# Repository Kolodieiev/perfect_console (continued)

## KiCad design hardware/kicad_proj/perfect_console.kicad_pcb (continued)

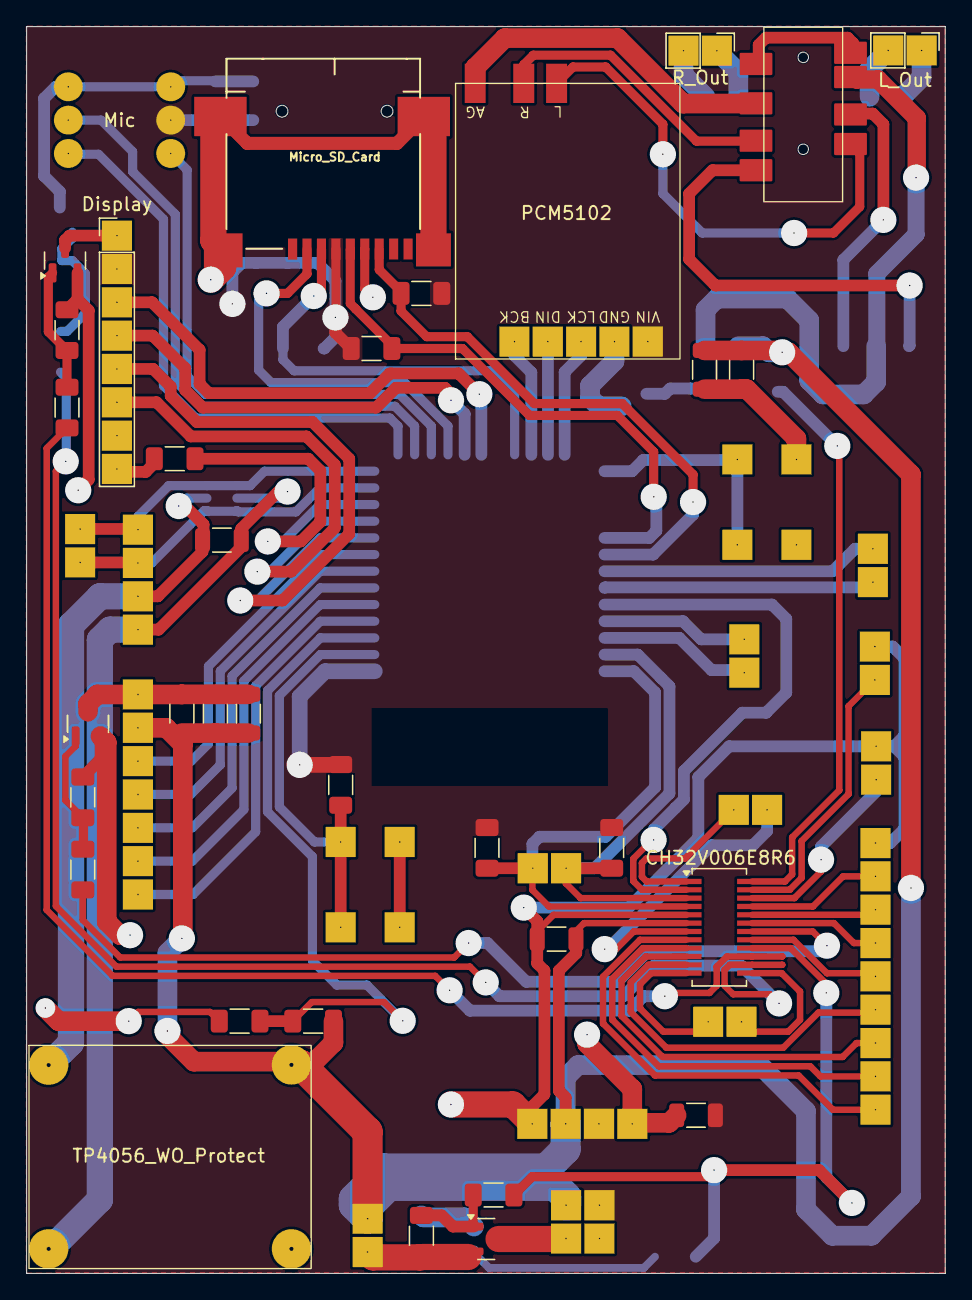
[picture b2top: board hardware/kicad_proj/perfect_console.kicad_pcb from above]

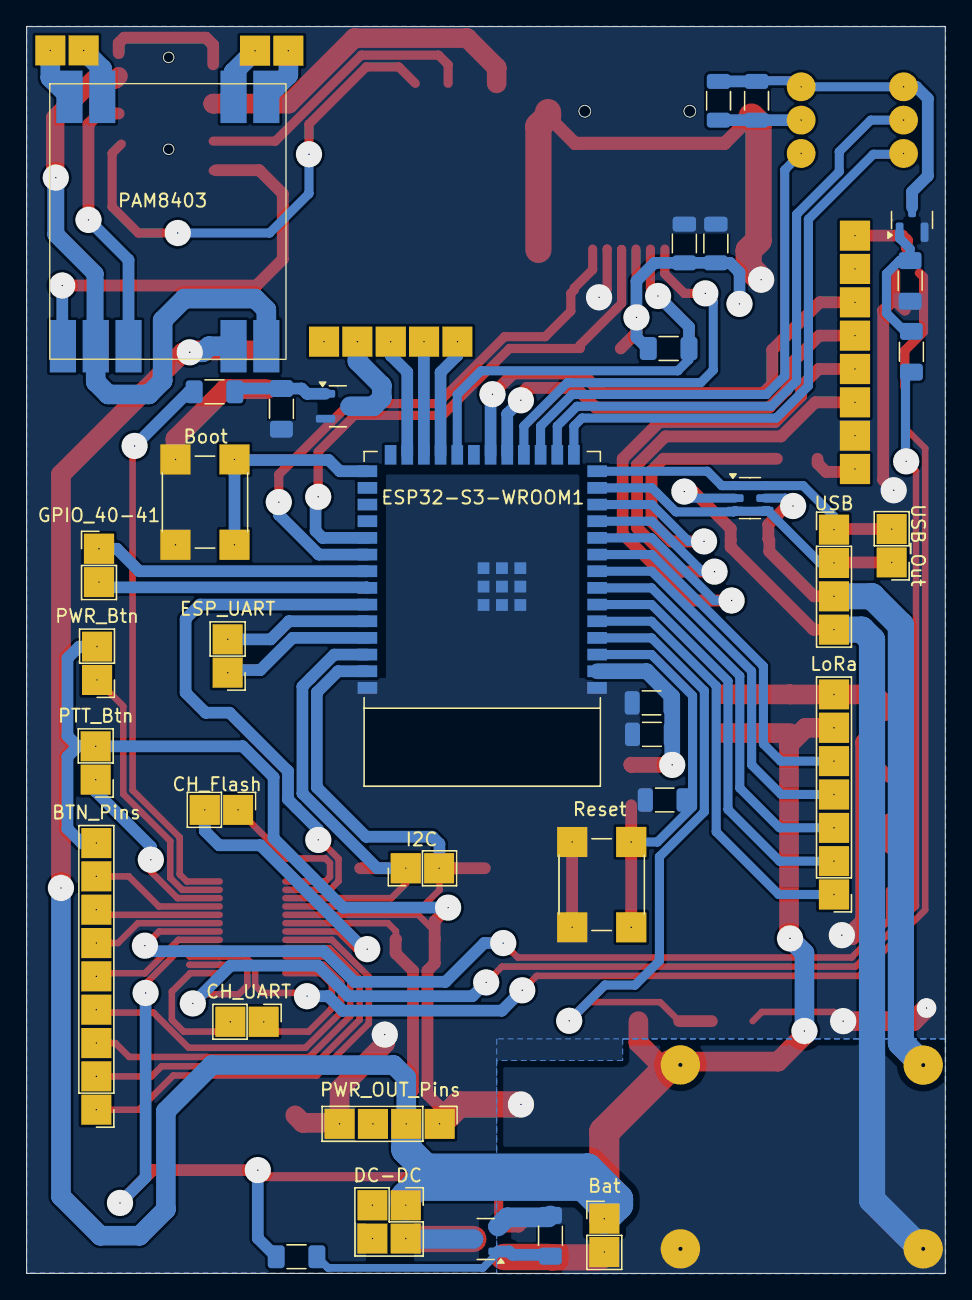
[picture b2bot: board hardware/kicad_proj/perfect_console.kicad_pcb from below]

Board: 2 copper layers, 70.0 x 95.0 mm, 70 parts (36 on the bottom side), 78 nets.

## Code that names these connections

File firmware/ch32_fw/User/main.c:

#include <debug.h>
#include <gpio.h>
#include <i2c_slave.h>
#include "input.h"
#include "touch.h"
#include "CoprocessorCMD.h"

// #define DEBUG_LOG

//------------------------------------------------------------------------------------------------------------- btns
#define BTNS_NUM 7

#define PIN_POWER_BTN 23

#define PIN_PTT_BTN 22
#define PIN_OK_BTN 19
#define PIN_BACK_BTN 8
#define PIN_LEFT_BTN 11
#define PIN_RIGHT_BTN 17
#define PIN_UP_BTN 9
#define PIN_DOWN_BTN 10

#define PIN_PB1 20
#define PIN_PB3 21

#define INPUT_UPD_TIME_MS 10

//------------------------------------------------------------------------------------------------------------- keys
#define PIN_MIC_KEY 14
#define PIN_DISPLAY_KEY 15
#define PIN_POWER_KEY 16
#define PIN_LORA_KEY 18
#define PIN_AUDIO_OUT_KEY 24

#define PIN_I2C_INT 2

//------------------------------------------------------------------------------------------------------------- i2c

#define BTNS_NUM_BUFF_SIZE ((BTNS_NUM + 7) / 8)
#define I2C_TEMP_BUFF_SIZE 5

#define I2C_FREQ 100000
#define RX_ADDR 0x66

//

volatile uint8_t _data_size_to_send = 0;
uint8_t _i2c_out_buff[I2C_TEMP_BUFF_SIZE] = {0};
uint8_t _btns_state_buff[BTNS_NUM_BUFF_SIZE] = {0};

//------------------------------------------------------------------------------------------------------------- power
#define TIME_TO_TOGGLE_PWR 3000
uint8_t _is_sleeping = 0;

//------------------------------------------------------------------------------------------------------------- func
void initPins (void);
void deinitPins (void);

void initPwrBtnExti (void);
void deinitPwrBtnExti (void);

void goToSleep (void);
void wakeUp (void);
void EXTI7_0_IRQHandler (void) __attribute__ ((interrupt ("WCH-Interrupt-fast")));

void i2c_read_handler (const uint8_t *in_buff, uint8_t in_buff_size);
void i2c_write_handler (uint8_t *out_buff, volatile uint8_t *out_buff_size);

int main (void) {
    NVIC_PriorityGroupConfig (NVIC_PriorityGroup_1);
    SystemCoreClockUpdate();
    initMillis();
    initUsartPrintf (230400);

    //-----------------------

#ifdef DEBUG_LOG
    printf ("Begin...\r\n");
#endif

    pinMode (PIN_POWER_BTN, GPIO_Mode_IPU);
    initPins();
    enableI2CSlave (I2C_FREQ, RX_ADDR, i2c_read_handler, i2c_write_handler);
    goToSleep();

    unsigned long power_btn_press_time = 0;

    while (1) {
        if (_is_sleeping == 1) {
            if (digitalRead (PIN_POWER_BTN) == HIGH) {
                power_btn_press_time = 0;
#ifdef DEBUG_LOG
                printf ("PIN_POWER_BTN == HIGH\r\n");
#endif
                goToSleep();
            } else {
                if (power_btn_press_time == 0) {
                    power_btn_press_time = millis();
                } else if (millis() - power_btn_press_time > TIME_TO_TOGGLE_PWR) {
                    power_btn_press_time = 0;
                    wakeUp();
                }
            }

            continue;
        }

        if (digitalRead (PIN_POWER_BTN) == LOW) {
            if (power_btn_press_time == 0) {
                power_btn_press_time = millis();
            } else if (millis() - power_btn_press_time > TIME_TO_TOGGLE_PWR) {
                power_btn_press_time = 0;
                goToSleep();
            }

            continue;
        } else {
            power_btn_press_time = 0;
        }

        static unsigned long input_update_time = 0;
        if (millis() - input_update_time > INPUT_UPD_TIME_MS) {
            inputUpdate();
            loadInputState (_btns_state_buff);
            input_update_time = millis();
        }
    }
}

void initPins (void) {
#ifdef DEBUG_LOG
    printf ("initPins\r\n");
#endif

    pinMode (PIN_POWER_KEY, GPIO_Mode_Out_PP);
    digitalWrite (PIN_POWER_KEY, HIGH);

    pinMode (PIN_DISPLAY_KEY, GPIO_Mode_Out_PP);
    digitalWrite (PIN_DISPLAY_KEY, LOW);

    pinMode (PIN_AUDIO_OUT_KEY, GPIO_Mode_Out_PP);
    digitalWrite (PIN_AUDIO_OUT_KEY, LOW);

    pinMode (PIN_MIC_KEY, GPIO_Mode_Out_PP);
    digitalWrite (PIN_MIC_KEY, LOW);

    pinMode (PIN_LORA_KEY, GPIO_Mode_Out_PP);
    digitalWrite (PIN_LORA_KEY, LOW);

    enableInput (BTNS_NUM);

    addInputBtn (PIN_PTT_BTN);
    addInputBtn (PIN_OK_BTN);
    addInputBtn (PIN_BACK_BTN);
    addInputBtn (PIN_LEFT_BTN);
    addInputBtn (PIN_RIGHT_BTN);
    addInputBtn (PIN_UP_BTN);
    addInputBtn (PIN_DOWN_BTN);

    // addInputTouchBtn (PIN_OK_BTN);
    // addInputTouchBtn (PIN_BACK_BTN);
    // addInputTouchBtn (PIN_LEFT_BTN);
    // addInputTouchBtn (PIN_RIGHT_BTN);
    // addInputTouchBtn (PIN_UP_BTN);
    // addInputTouchBtn (PIN_DOWN_BTN);
}

void deinitPins (void) {
#ifdef DEBUG_LOG
    printf ("deinitPins\r\n");
#endif

    disableInput();
    disableTouchCap();

    pinMode (PIN_MIC_KEY, GPIO_Mode_IN_FLOATING);
    pinMode (PIN_DISPLAY_KEY, GPIO_Mode_IN_FLOATING);
    pinMode (PIN_POWER_KEY, GPIO_Mode_IN_FLOATING);
    pinMode (PIN_LORA_KEY, GPIO_Mode_IN_FLOATING);
    pinMode (PIN_AUDIO_OUT_KEY, GPIO_Mode_IN_FLOATING);
    pinMode (PIN_PTT_BTN, GPIO_Mode_IN_FLOATING);
    pinMode (PIN_OK_BTN, GPIO_Mode_IN_FLOATING);
    pinMode (PIN_BACK_BTN, GPIO_Mode_IN_FLOATING);
    pinMode (PIN_LEFT_BTN, GPIO_Mode_IN_FLOATING);
    pinMode (PIN_RIGHT_BTN, GPIO_Mode_IN_FLOATING);
    pinMode (PIN_UP_BTN, GPIO_Mode_IN_FLOATING);
    pinMode (PIN_DOWN_BTN, GPIO_Mode_IN_FLOATING);
}

void initPwrBtnExti (void) {
    RCC_PB2PeriphClockCmd (RCC_PB2Periph_AFIO, ENABLE);

    EXTI_InitTypeDef EXTI_InitStructure = {0};
    GPIO_EXTILineConfig (GPIO_PortSourceGPIOB, GPIO_PinSource1);
    EXTI_InitStructure.EXTI_Line = EXTI_Line1;
    EXTI_InitStructure.EXTI_Mode = EXTI_Mode_Interrupt;
    EXTI_InitStructure.EXTI_Trigger = EXTI_Trigger_Falling;
    EXTI_InitStructure.EXTI_LineCmd = ENABLE;
    EXTI_Init (&EXTI_InitStructure);

    NVIC_InitTypeDef NVIC_InitStructure = {0};
    NVIC_InitStructure.NVIC_IRQChannel = EXTI7_0_IRQn;
    NVIC_InitStructure.NVIC_IRQChannelPreemptionPriority = 1;
    NVIC_InitStructure.NVIC_IRQChannelSubPriority = 1;
    NVIC_InitStructure.NVIC_IRQChannelCmd = ENABLE;
    NVIC_Init (&NVIC_InitStructure);
}

void deinitPwrBtnExti (void) {
    EXTI_DeInit();
    NVIC_DisableIRQ (EXTI7_0_IRQn);
    RCC_PB2PeriphClockCmd (RCC_PB2Periph_AFIO, DISABLE);
}

void goToSleep (void) {
#ifdef DEBUG_LOG
    printf ("goToSleep\r\n");
#endif

    _is_sleeping = 1;
    initPwrBtnExti();
    deinitPins();
    PWR_EnterSTANDBYMode (PWR_STANDBYEntry_WFE);
}

void wakeUp (void) {
#ifdef DEBUG_LOG
    printf ("wakeUp\r\n");
#endif
    deinitPwrBtnExti();
    _is_sleeping = 0;
    initPins();
}

void EXTI7_0_IRQHandler (void) {
    if (EXTI_GetITStatus (EXTI_Line1) != RESET) {
#ifdef DEBUG_LOG
        printf ("EXTI\r\n");
#endif
        EXTI_ClearITPendingBit (EXTI_Line1);
    }
}

void i2c_read_handler (const uint8_t *in_buff, uint8_t in_buff_size) {
    CoprocessorCMD_t cmd = in_buff[0];
    switch (cmd) {
    case CCPU_CMD_GET_BTNS_STATE:
        memcpy (_i2c_out_buff, _btns_state_buff, BTNS_NUM_BUFF_SIZE);
        _data_size_to_send = BTNS_NUM_BUFF_SIZE;
        break;
    case CCPU_CMD_PIN_ON:
        if (in_buff_size < 2)
            return;
        digitalWrite (in_buff[1], HIGH);
        break;
    case CCPU_CMD_PIN_OFF:
        if (in_buff_size < 2)
            return;
        digitalWrite (in_buff[1], LOW);
        break;
    case CCPU_CMD_BTN_OFF:
        if (in_buff_size < 2)
            return;
        disableBtnByPos (in_buff[1]);
        break;
    case CCPU_CMD_BTN_ON:
        if (in_buff_size < 2)
            return;
        enableBtnByPos (in_buff[1]);
        break;
    case CCPU_CMD_DISABLE:
    case CCPU_CMD_ENABLE:
    default:
        return;
    }
}

void i2c_write_handler (uint8_t *out_buff, volatile uint8_t *out_buff_size) {
    *out_buff_size = _data_size_to_send;
    memcpy (out_buff, _i2c_out_buff, _data_size_to_send);
    for (uint32_t i = 0; i < _data_size_to_send; ++i)
        _i2c_out_buff[i] = 0;

    _data_size_to_send = 0;
}

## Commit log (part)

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2025-11-11 Незначні покращення
2025-11-11 Покращено взаємодію файлового менеджера з Linux
2025-11-12 Видалено TODO
2025-11-12 Додано головне ігрове меню
2025-11-12 Додано основні класи гри
2025-11-13 Перейменовано в RpgBaseScene
2025-11-13 Додано структуру для загального опису рівня
2025-11-13 Додано завантаження ресурсів рівня з диску
2025-11-13 Розширено тип маски прохідності спрайту
2025-11-13 Додано тип плитки
2025-11-14 Логування без перенесення рядка
2025-11-14 Виправлено ім'я задля уникнення перевантаження
2025-11-15 Видалено непотрібні файли
2025-11-15 Видалено неактуальні прапори збірки
2025-11-15 Виправлено некоректні параметри відкриття файлів
2025-11-15 Додано автоматичний завантажувач ресурсів поверхні
    Додано автоматичний завантажувач ресурсів поверхні сцени з диску.
2025-11-15 Додано повідомлення про відсутній ресурс
2025-11-15 Виправлено розміщення спрайтів
2025-11-15 Додано об'єкт персонажа
2025-11-15 Додано завантаження поверхні
2025-11-15 Видалено непотрібний параметр
    Менеджер ресурсів вже оголошено глобально
2025-11-15 Додано перевірку на 0 ідентифікатор
2025-11-15 Додано спрайт героя
2025-11-15 Додано скріншот
2025-12-22 Виправлено помилки в прикладі Lua
2025-12-22 Виправлено логіку малювання віджетів
2025-12-22 Виправлено помилку встановлення зображення
2025-12-22 Рефакторинг
2025-12-27 Виправлено(уточнено) імена методів
2025-12-28 Перенесено в контекст Lua
2025-12-28 Виправлення потенційних помилок
2025-12-28 Виправлено приведення типів до стилю С++
2025-12-28 Додано приклад роботи з SD
2025-12-28 Виправлено помилку, яка псувала купу
2026-01-06 Додано переривання надсилання файлу
2026-01-06 Додано прокручування тексту
2026-01-06 Виправлено документацію
2026-01-06 Додано відсутнє копіювання поля
2026-01-11 Видалено недосяжний код
2026-01-11 Магічні значення змінено на іменовані визначення
2026-01-11 Додано більше темного значення до кольору
2026-01-11 Виправлено помилку малювання фону
2026-01-12 Покращено сторінку надсилання файлу
2026-01-12 Зменшено глибину вкладення
2026-01-12 Додано відображення IP
2026-01-12 Додано фонове отримання файлів
2026-01-12 Виправлено логіку
2026-01-12 Видалено невикористану змінну
2026-01-13 Виправлено ім'я методу
2026-01-13 Імена функцій переміщено в масив
2026-01-13 Імена функцій переміщено до масиву
2026-01-13 Прибрано непотрібний else
2026-01-13 Додано обгортку для керування WiFi з Lua
2026-01-14 Виправлено методи
2026-01-16 Виправлено ім'я функції для уніфікації
2026-01-16 Виправлено помилку в прикладі
2026-01-16 Додано приклад керування wifi та запитів до web
2026-01-16 Додано return при некоректній к-сті параметрів
2026-01-16 Додано обгортку для Lua-serial
2026-01-16 Додано обгортку для Lua-web
2026-01-17 Переміщено в namespace
2026-01-18 Додано документацію
2026-01-18 Скорочено ланцюжок викликів
2026-01-19 Метод ініціалізації зроблено статичним
2026-01-19 Виклик методу замінено визначенням
2026-01-19 Оновлено підключення FileStream
2026-01-19 Додано підключення cstring
2026-01-20 Видалено статичність змінної
2026-01-20 Виправлено підключення FileStream
2026-01-20 Додано статичність методу
2026-01-20 Видалено неактуальний readme
2026-01-20 Налаштування об'єднано в graphics_setup.h
2026-01-21 Рефакторинг + документація
2026-01-21 Документація + рефакторинг
2026-01-23 Покращено документацію
2026-01-24 Виправлено некоректне визначення constexpr функції
2026-01-25 Виправлено ім'я типу
2026-01-25 Рефакторинг та документація
2026-01-25 MenuItem тепер потребує власний Image
2026-01-25 Додано перевірку типу вхідного об'єкта
2026-01-26 Виправлено шлях до зображення
2026-01-26 Додано перевірку належності до типу
2026-01-26 Додано readme
2026-01-26 Придушено попередження
2026-01-27 Додано підтримку завантаження списку файлів
2026-01-27 Неактуальний коментар
2026-01-29 Додано адаптивність форми
2026-01-29 Переписано на прямі виклики POSIX
2026-01-29 Додано підтримку видалення файлів
2026-01-30 Код WebServer додано в проект
2026-01-30 Усунуто спрацювання WDT
2026-01-30 Додано підтримку передзавантаження даних
2026-01-30 Оновлено розмір буферів сервера
2026-01-30 Приведено до коректного вигляду
2026-01-30 Виправлено русизми
2026-01-31 Додано правило для швидкої збірки
2026-02-01 Додано каркас документації
2026-02-01 Додано шаблон для майбутньої документації
2026-02-01 Додано про проєкт
2026-02-01 Оновлено Readme
2026-02-01 Виправлено тип заголовку
2026-02-02 Тему змінено на Furo
2026-02-06 Додано налаштування частоти ядра
2026-02-06 Додано підсвітку коду
2026-02-06 Додано визначення
2026-02-07 Видалено зайві відступи
2026-02-07 Налаштування відокремлено від фреймворку
2026-02-07 Виправлено шлях в include
2026-02-07 Додано новий каталог з налаштуваннями
2026-02-08 Спрощено виклик монтування карти пам'яті
2026-02-10 Виправлено вимкнення кнопок
2026-02-10 Виправлено некоректну логіку
2026-02-10 Видалено номер версії
2026-02-10 Уточнено опис класу
2026-02-10 Уточнено документацію
2026-02-11 Виправлено звернення до висячого вказівника
2026-02-14 Явно вказано версію C++
2026-02-14 Commit a63bfd9
2026-02-14 Commit 8440ae6
2026-02-14 Покращено перевірку монтування SD
2026-02-14 Видалено підтримку Doxygen
2026-02-14 Виправлено документацію методу
2026-02-14 Виправлено помилку в документації
2026-02-15 Виправлено документацію методів
2026-02-15 Покращено обробку читання хідера
2026-02-15 Додано відсутнє скидання прапору
2026-02-15 Видалено параметр за замовчуванням
2026-02-15 Виправлено місце встановлення прапору
2026-02-15 Додано документацію файлового менеджера
2026-02-18 Спрощено структуру каталогів
2026-02-18 Зменшено глибину вкладення каталогів
2026-02-18 Оновлено структуру проєкту Pixeler
2026-02-18 Виправлено шлях
2026-02-18 Додано перевірку відкриття файла
2026-02-20 Виправлено імена полів класу
2026-02-20 Об'єднано два методи отримання IP
2026-02-20 Оновлено ім'я методу
2026-02-20 Додано обробку некоректних значень
2026-02-20 Обробку винесено до WiFiManager
2026-02-20 Видалено зайву інформацію про помилку
2026-02-20 Додано налаштування потужності WiFi
2026-02-21 Додано завантаження налаштувань потужності модуля
2026-02-21 Видалено неактуальні рядкі
2026-02-21 Спрощено створення однотипного Label
2026-02-21 Спрощено генерацію Label для заголовка вікна
2026-02-21 Додано перевірку mutex-а
2026-02-21 Перейменовано AutoLock в MutexGuard
2026-02-21 Видалено блоки try-catch
2026-02-21 Виправлено перевірку mutex-a
2026-02-21 Додано значення за замовченням
2026-02-21 Виправлено налаштування cpp-check
2026-02-21 Виправлено попередження cpp-check
2026-02-21 Видалено невикористані поля
2026-02-22 Оновлено гербер-файли
2026-02-22 Додано маркування мосфетів
2026-02-22 Зменшено розміри плати
2026-02-22 Видалено креслення для ручного виготовлення
2026-03-15 Видалено непотрібний flush
2026-03-15 Додано відсутню залежність для Windows
2026-03-15 Видалено неактуальний todo
2026-03-15 Додано налаштування інвертування кольорів пікселів
2026-03-16 Виправлено редефайн
2026-03-16 Виправлено чергу команд ініціалізації дисплея
2026-03-16 Видалено дублювання коду
2026-03-16 Додано відсутнє взяття мютекса
2026-03-16 Додано метод отримання мютекса синхронізації
2026-03-16 Видалено перевірку малоймовірного випадку
2026-03-16 Додано підтримку декількох пристроїв на одному SPI
2026-03-17 Оновлено документацію
2026-03-17 Додано початкову ініціалізацію
2026-03-17 Видалено непотрібний sizeof
2026-03-17 Виправлено зміщення тексту
2026-03-20 Виправлено приклад lua-pwm
2026-03-20 Видалено приведення типу
2026-03-22 Зменшено значення одночасно відкритих файлів
2026-03-22 Видалено непотрібний include
2026-03-22 Увімкнуто вивід інформаційних повідомлень в термінал
2026-03-22 Покращено обробку ініціалізації шини SPI
2026-03-22 Додано таблицю розділів для esp32
2026-03-22 Додано сканер шини i2c
2026-03-23 Додано базовий клас для драйвера сенсорних екранів
2026-03-23 Додано підтримку сенсорних екранів в систему вводу
2026-03-23 Додано читання/запис з двобайтовою командою
2026-03-23 Виправлено імена методів менеджера i2c
2026-03-23 Додано пошук віджета за екранними координатами
2026-03-23 Додано інформацію про сенсорний ввід
2026-03-23 Додано налаштування сенсорного вводу
2026-03-24 Виправлено драйвер сенсорного екрана JC3248W535C
2026-03-24 Виправлено драйвер сенсорного екрана GT911
2026-03-24 Додано перевірку підключення сенсорного екрану
2026-03-24 Відключено підтримку сенсорного екрану в прошивці
2026-03-25 Виправлено прапор збірки
2026-03-26 Виправлено імена методів
2026-03-26 Виправлено розрахунок тривалості треку
2026-03-26 Видалено float операції
2026-03-26 Оптимізовано отримання семплу
2026-03-26 Додано підтримку сенсорного екрану
2026-03-28 Повернуто fluch перед відключенням підсвітки
2026-03-28 Видалена залежність віджетів від ширини дисплиє
2026-03-28 Переміщено затримку між викликами update
2026-03-28 Додано підтримку керування живленням sd-карти
2026-03-28 fix: віджети не компілювалися з вимкнутою графікою
2026-03-28 fix: Методи для взаємодії з графікою доступні без неї
2026-03-31 Виправлено ім'я метода
2026-03-31 Видалено надлишкову спадковість
2026-03-31 Виправлено синтаксичну помилку в документації
2026-03-31 Виправлено синтаксичну помилку в коментарі
2026-03-31 Додано підтримку SD_MMC
2026-03-31 Покращено імена визначень
2026-03-31 Покращено імена визначень. Додано приклади
2026-03-31 Повертнуто загублений include
2026-03-31 Додано нагадування про ревізію P4
2026-03-31 Оновлено документацію файлового менеджера
2026-04-03 Розділено ширину UI та ширину дисплея
2026-04-03 Оновлено ліцензію
2026-04-03 Виправлено налаштування
2026-04-03 Додано підтримку PPA для P4
2026-04-03 Видалено неактуальний return
2026-04-03 Додано підтримку псевдопрозорості плитки
2026-04-03 Додано заглушку, якщо графіку вимкнено
2026-04-03 Очистка від зайвих директив препроцесора
2026-04-03 Видалено підтримку gfxfont
2026-04-03 Видалено підтримку "round mode"
2026-04-03 Методи PPA переміщено до головного класу
2026-04-03 Видалено підтримку "round mode" та gfxfont
2026-04-03 Додано звільнення пам'яті буфера кадру
2026-04-07 Оптимізація використання пам'яті
2026-04-07 Оновлено бібліотеку аудіо
2026-04-07 Заміна abs на builtin варіант
2026-04-07 Виправлено поведінку виводу тексту
2026-04-07 Покращено можливості
2026-04-07 Читання рядка з файлу винесено до FileManager
2026-04-07 Додано повідомлення про неініціалізований стан
2026-04-07 Додано керування обмеженням площі виводу тексту
2026-04-07 Додано відсутній __unload
2026-04-07 Реєстрацію модулів переміщено до LuaContext
2026-04-07 Додано автоматичне підключення до WiFi
2026-04-07 Додано режим інтернет-радіо
2026-04-07 Зменшено кількість рядків на сторінку
2026-04-07 Виправлено значення рядків
2026-04-12 Виправлено позиціонування тексту без прокручування
2026-04-12 Виправлено позиціонування тексту по вертикалі
2026-04-12 fix: Відсутнє оновлення після зміни типу поля
2026-04-12 Додано налаштування vu метра
2026-04-12 Додано vu-метр
2026-04-13 fix: Некоректно встановлюється курсор
2026-04-13 upd: Оновлено підхід до формування віджета
2026-04-13 Скорочено повідомлення про помилку Lua
2026-04-13 Виправлено позиціонування повідомлення
2026-04-15 Додано зображення в документацію
2026-04-15 Оновлено вимоги до версії С++
2026-04-15 Оновлено ім'я файлу
2026-04-15 Приклади видалено на доопрацювання
2026-04-15 Виправлено тип перечислення
2026-04-15 Виправлено відповідно до нової архітектури рушія
2026-04-16 Додано порожній рядок в кінці файла
2026-04-16 Перейменовано для однакового стилю іменування
2026-04-16 Змінено імена класів, що відповідають за шини
2026-04-16 Оновлено архітектуру управління ресурсами
2026-04-16 Змінено місце в структурі проєкту
2026-04-16 Оновлено ім'я класу керування шиною SPI
2026-04-16 Змінено ім'я методу SPI_Bus::initBus на SPI_Bus::init
2026-04-16 Оновлено структуру файлів ігрового рушія
2026-04-26 Методи повороту зображення оголошено public
2026-04-26 Виправлено виклик __bswap16 для кросплатформи
2026-04-26 Видалено повідомлення про ppa
2026-04-26 feat: Підтримка зміщення фонового зображення
2026-04-26 upd: Замінено контейнери об'єктів для оптимізації
2026-04-26 Замінено повідомлення про помилку алокації
2026-04-26 Виправлено ім'я класа
2026-04-26 feat: Додано гру Шахи
